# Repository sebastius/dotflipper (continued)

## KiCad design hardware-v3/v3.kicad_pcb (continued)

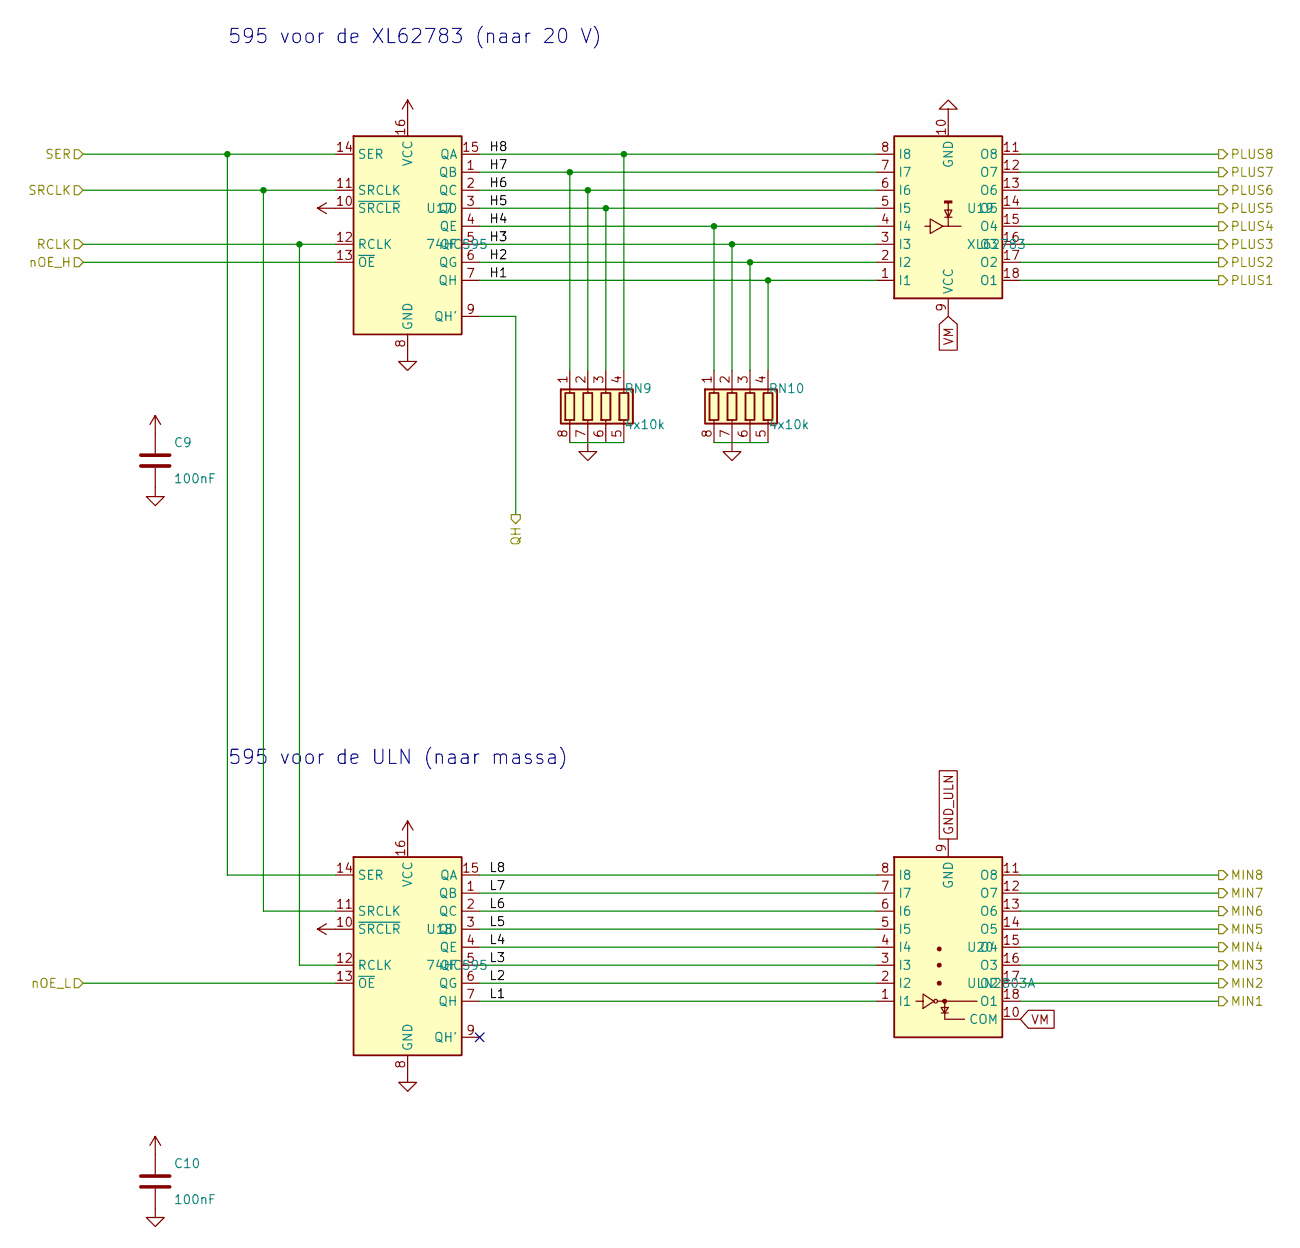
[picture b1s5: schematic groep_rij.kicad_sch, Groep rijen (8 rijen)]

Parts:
C9, C10: 100nF; C_0603_1608Metric; LCSC C14663
RN9, RN10: 4x10k; R_Array_Convex_4x0603; LCSC C29718
U17, U18: 74HC595; SOIC-16_3.9x9.9mm_P1.27mm; LCSC C5947
U19: XL62783; SOIC-18W_7.5x11.6mm_P1.27mm; LCSC C556260
U20: ULN2803A; SOIC-18W_7.5x11.6mm_P1.27mm; LCSC C845537

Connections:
+5V: C9.1, C10.1, U17.10 (~SRCLR), U17.16 (VCC), U18.10 (~SRCLR), U18.16 (VCC); also elsewhere on the board
/CHAIN4: U17.14 (SER), U18.14 (SER); also elsewhere on the board
/CHAIN5: U17.9 (QH'); also elsewhere on the board
/G5/H1: RN10.4 (R4.1), U17.7 (QH), U19.1 (I1)
/G5/H2: RN10.3 (R3.1), U17.6 (QG), U19.2 (I2)
/G5/H3: RN10.2 (R2.1), U17.5 (QF), U19.3 (I3)
/G5/H4: RN10.1 (R1.1), U17.4 (QE), U19.4 (I4)
/G5/H5: RN9.3 (R3.1), U17.3 (QD), U19.5 (I5)
/G5/H6: RN9.2 (R2.1), U17.2 (QC), U19.6 (I6)
/G5/H7: RN9.1 (R1.1), U17.1 (QB), U19.7 (I7)
/G5/H8: RN9.4 (R4.1), U17.15 (QA), U19.8 (I8)
/G5/L1: U18.7 (QH), U20.1 (I1)
/G5/L2: U18.6 (QG), U20.2 (I2)
/G5/L3: U18.5 (QF), U20.3 (I3)
/G5/L4: U18.4 (QE), U20.4 (I4)
/G5/L5: U18.3 (QD), U20.5 (I5)
/G5/L6: U18.2 (QC), U20.6 (I6)
/G5/L7: U18.1 (QB), U20.7 (I7)
/G5/L8: U18.15 (QA), U20.8 (I8)
/LATCH: U17.12 (RCLK), U18.12 (RCLK); also elsewhere on the board
/SCLK: U17.11 (SRCLK), U18.11 (SRCLK); also elsewhere on the board
/X3_1: U19.11 (O8); also elsewhere on the board
/X3_2: U20.11 (O8); also elsewhere on the board
/X3_3: U19.12 (O7); also elsewhere on the board
/X3_4: U20.12 (O7); also elsewhere on the board
/X3_5: U19.13 (O6); also elsewhere on the board
/X3_6: U20.13 (O6); also elsewhere on the board
/X3_7: U19.14 (O5); also elsewhere on the board
/X3_8: U20.14 (O5); also elsewhere on the board
/X3_9: U19.15 (O4); also elsewhere on the board
/X3_10: U20.15 (O4); also elsewhere on the board
/X3_11: U19.16 (O3); also elsewhere on the board
/X3_12: U20.16 (O3); also elsewhere on the board
/X3_13: U19.17 (O2); also elsewhere on the board
/X3_14: U20.17 (O2); also elsewhere on the board
/X3_15: U19.18 (O1); also elsewhere on the board
/X3_16: U20.18 (O1); also elsewhere on the board
/nOE_H_ROW: U17.13 (~OE); also elsewhere on the board
/nOE_L_ROW: U18.13 (~OE); also elsewhere on the board
GND: C9.2, C10.2, RN9.5 (R4.2), RN9.6 (R3.2), RN9.7 (R2.2), RN9.8 (R1.2), RN10.5 (R4.2), RN10.6 (R3.2), RN10.7 (R2.2), RN10.8 (R1.2), U17.8 (GND), U18.8 (GND), U19.10 (GND); also elsewhere on the board
GND_ULN: U20.9 (GND); also elsewhere on the board
VM: U19.9 (VCC), U20.10 (COM); also elsewhere on the board

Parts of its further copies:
C11, C12: 100nF; C_0603_1608Metric; LCSC C14663
RN11, RN12: 4x10k; R_Array_Convex_4x0603; LCSC C29718
U21, U22: 74HC595; SOIC-16_3.9x9.9mm_P1.27mm; LCSC C5947
U23: XL62783; SOIC-18W_7.5x11.6mm_P1.27mm; LCSC C556260
U24: ULN2803A; SOIC-18W_7.5x11.6mm_P1.27mm; LCSC C845537

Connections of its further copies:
+5V: C11.1, C12.1, U21.10 (~SRCLR), U21.16 (VCC), U22.10 (~SRCLR), U22.16 (VCC); also elsewhere on the board
/CHAIN5: U21.14 (SER), U22.14 (SER); also elsewhere on the board
/CHAIN_END: U21.9 (QH'); also elsewhere on the board
/G6/H1: RN12.4 (R4.1), U21.7 (QH), U23.1 (I1)
/G6/H2: RN12.3 (R3.1), U21.6 (QG), U23.2 (I2)
/G6/H3: RN12.2 (R2.1), U21.5 (QF), U23.3 (I3)
/G6/H4: RN12.1 (R1.1), U21.4 (QE), U23.4 (I4)
/G6/H5: RN11.3 (R3.1), U21.3 (QD), U23.5 (I5)
/G6/H6: RN11.2 (R2.1), U21.2 (QC), U23.6 (I6)
/G6/H7: RN11.1 (R1.1), U21.1 (QB), U23.7 (I7)
/G6/H8: RN11.4 (R4.1), U21.15 (QA), U23.8 (I8)
/G6/L1: U22.7 (QH), U24.1 (I1)
/G6/L2: U22.6 (QG), U24.2 (I2)
/G6/L3: U22.5 (QF), U24.3 (I3)
/G6/L4: U22.4 (QE), U24.4 (I4)
/G6/L5: U22.3 (QD), U24.5 (I5)
/G6/L6: U22.2 (QC), U24.6 (I6)
/G6/L7: U22.1 (QB), U24.7 (I7)
/G6/L8: U22.15 (QA), U24.8 (I8)
/LATCH: U21.12 (RCLK), U22.12 (RCLK); also elsewhere on the board
/SCLK: U21.11 (SRCLK), U22.11 (SRCLK); also elsewhere on the board
/X2_1: U23.11 (O8); also elsewhere on the board
/X2_2: U24.11 (O8); also elsewhere on the board
/X2_3: U23.12 (O7); also elsewhere on the board
/X2_4: U24.12 (O7); also elsewhere on the board
/X2_5: U23.13 (O6); also elsewhere on the board
/X2_6: U24.13 (O6); also elsewhere on the board
/X2_7: U23.14 (O5); also elsewhere on the board
/X2_8: U24.14 (O5); also elsewhere on the board
/X2_9: U23.15 (O4); also elsewhere on the board
/X2_10: U24.15 (O4); also elsewhere on the board
/X2_11: U23.16 (O3); also elsewhere on the board
/X2_12: U24.16 (O3); also elsewhere on the board
/X2_13: U23.17 (O2); also elsewhere on the board
/X2_14: U24.17 (O2); also elsewhere on the board
/X2_15: U23.18 (O1); also elsewhere on the board
/X2_16: U24.18 (O1); also elsewhere on the board
/nOE_H_ROW: U21.13 (~OE); also elsewhere on the board
/nOE_L_ROW: U22.13 (~OE); also elsewhere on the board
GND: C11.2, C12.2, RN11.5 (R4.2), RN11.6 (R3.2), RN11.7 (R2.2), RN11.8 (R1.2), RN12.5 (R4.2), RN12.6 (R3.2), RN12.7 (R2.2), RN12.8 (R1.2), U21.8 (GND), U22.8 (GND), U23.10 (GND); also elsewhere on the board
GND_ULN: U24.9 (GND); also elsewhere on the board
VM: U23.9 (VCC), U24.10 (COM); also elsewhere on the board

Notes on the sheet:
595 voor de XL62783 (naar 20 V)
595 voor de ULN (naar massa)

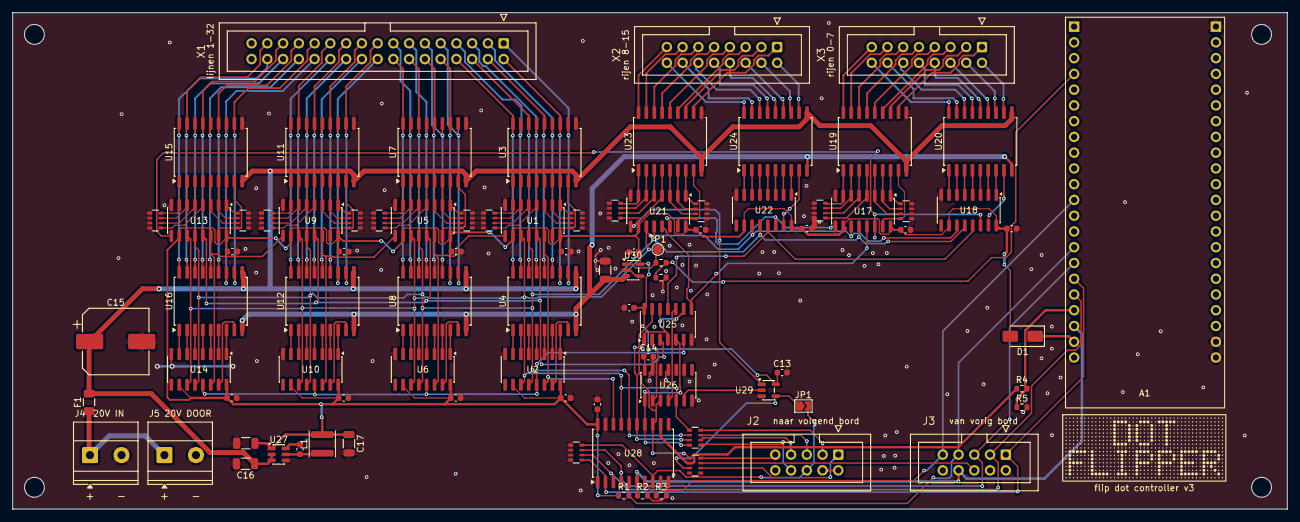
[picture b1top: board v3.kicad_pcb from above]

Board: 2 copper layers, 205.4 x 80.0 mm, 93 parts (0 on the bottom side), 206 nets.

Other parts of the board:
H1, H2, H3, H4: MountingHole_3.2mm_M3
LOGO1: Logo_Dotflipper

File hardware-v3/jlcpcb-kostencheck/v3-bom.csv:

Comment,Designator,Footprint,LCSC Part #
100nF,"C1,C10,C11,C12,C13,C14,C18,C19,C2,C20,C3,C4,C5,C6,C7,C8,C9",C_0603_1608Metric,C14663
470uF 35V,C15,CP_Elec_10x10.5,C46550413
10uF 50V,C16,C_1206_3216Metric,C13585
22uF 25V,"C17,C21",C_1206_3216Metric,C12891
SS14,D1,D_SMA,C2480
3A,F1,Fuse_1206_3216Metric,C182445
4.7uH,L1,L_Sunlord_SWPA4030S,C57269
10k,"R1,R4",R_0603_1608Metric,C25804
100k,"R2,R3",R_0603_1608Metric,C25803
20k,R5,R_0603_1608Metric,C4184
4x10k,"RN1,RN10,RN11,RN12,RN15,RN2,RN3,RN4,RN5,RN6,RN7,RN8,RN9",R_Array_Convex_4x0603,C29718
4x1k,"RN13,RN14",R_Array_Convex_4x0603,C20197
ULN2803A,"U12,U16,U20,U24,U4,U8",SOIC-18W_7.5x11.6mm_P1.27mm,C845537
XL62783,"U11,U15,U19,U23,U3,U7",SOIC-18W_7.5x11.6mm_P1.27mm,C556260
74HC32,U25,SOIC-14_3.9x8.7mm_P1.27mm,C5632
74HC14,U26,SOIC-14_3.9x8.7mm_P1.27mm,C5605
AP63205WU,U27,TSOT-23-6,C2071056
74AHCT541,U28,SOIC-20W_7.5x12.8mm_P1.27mm,C2682058
74LVC1G79,U29,SOT-23-5,C42878
74HC595,"U1,U10,U13,U14,U17,U18,U2,U21,U22,U5,U6,U9",SOIC-16_3.9x9.9mm_P1.27mm,C5947

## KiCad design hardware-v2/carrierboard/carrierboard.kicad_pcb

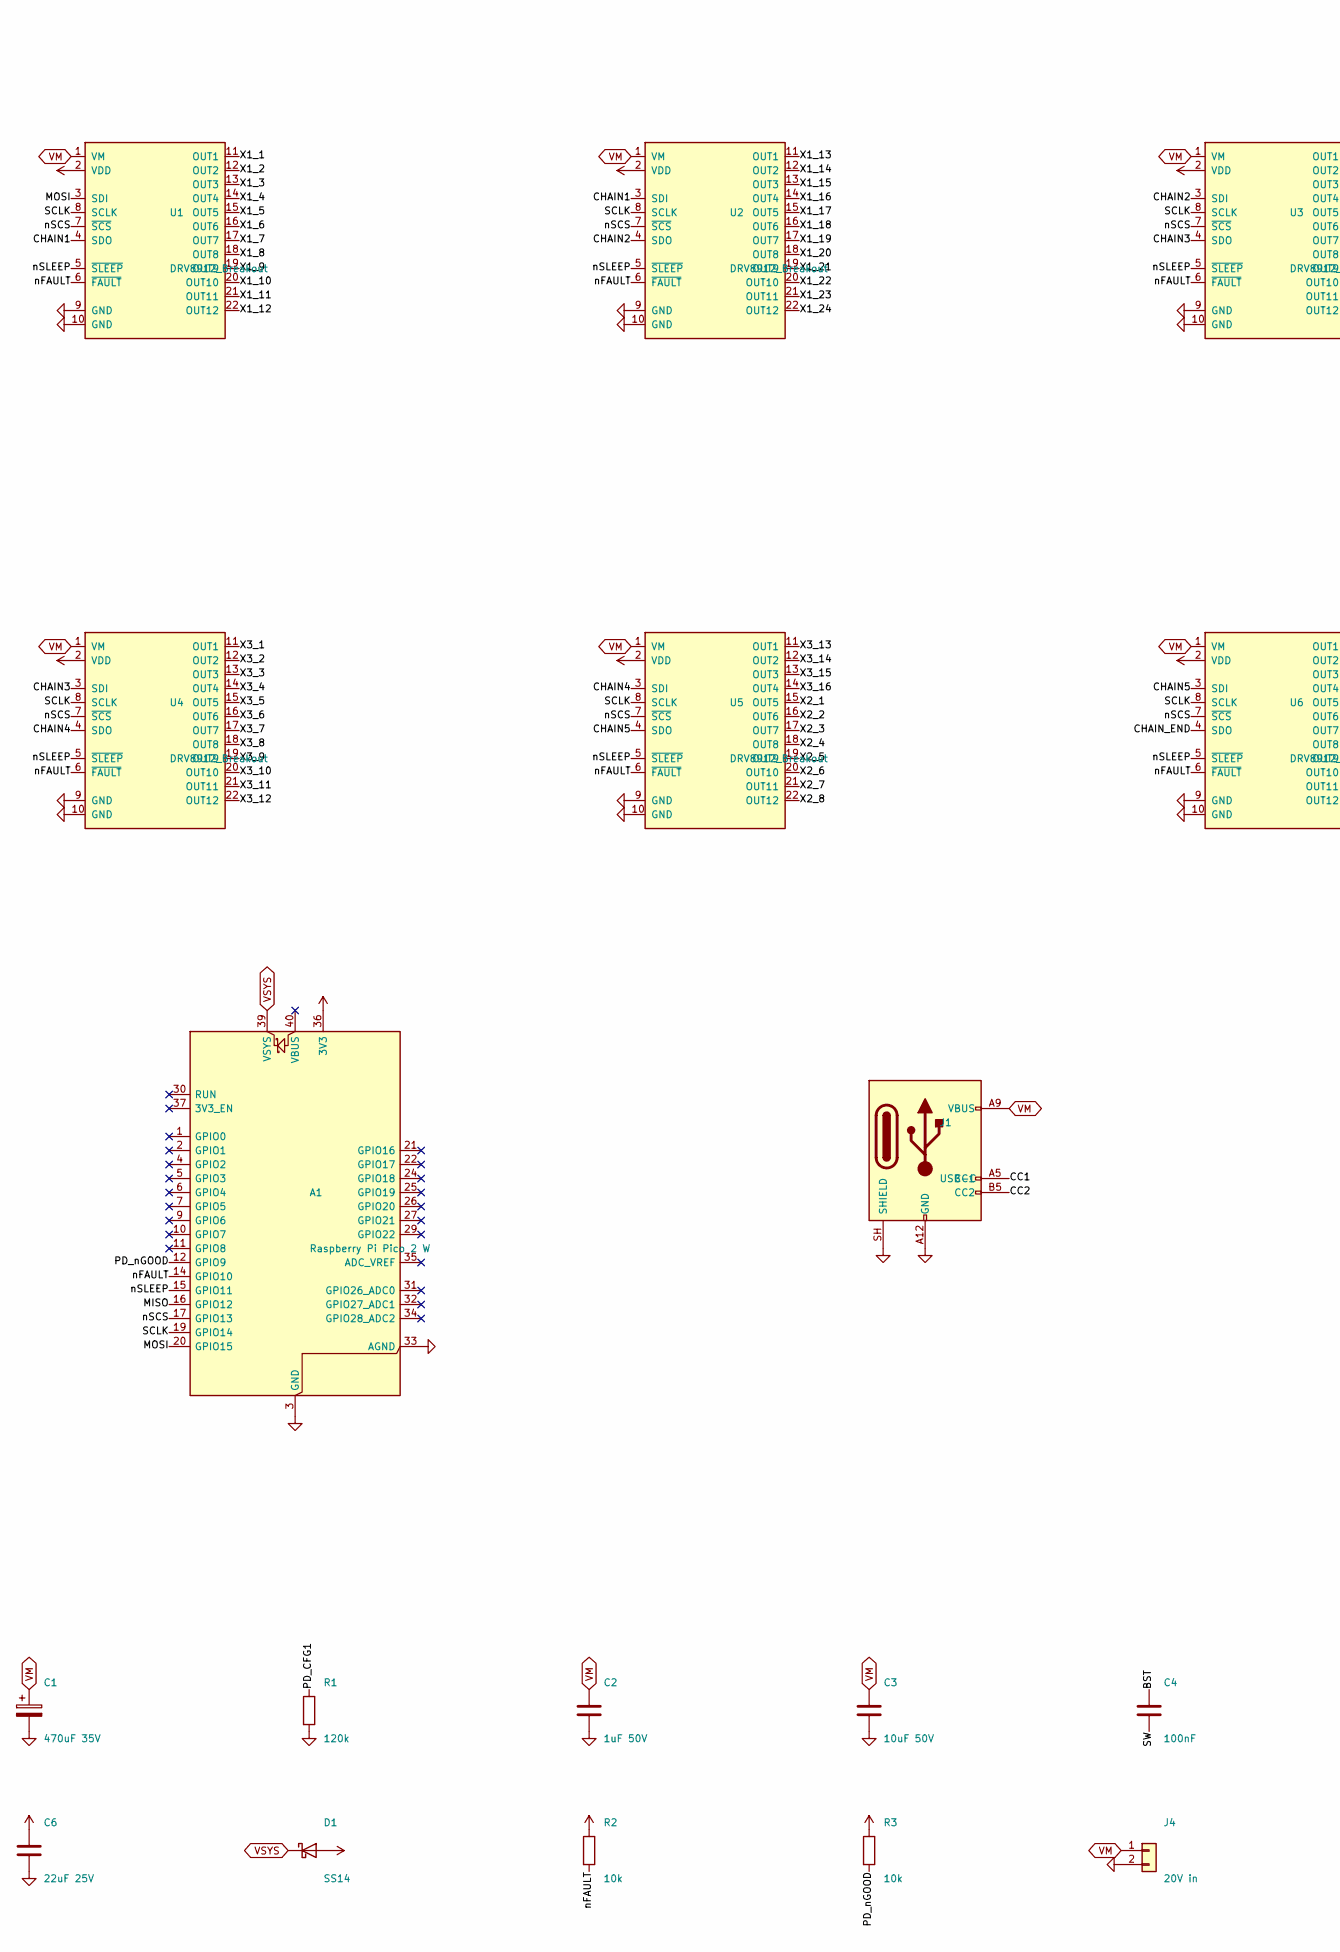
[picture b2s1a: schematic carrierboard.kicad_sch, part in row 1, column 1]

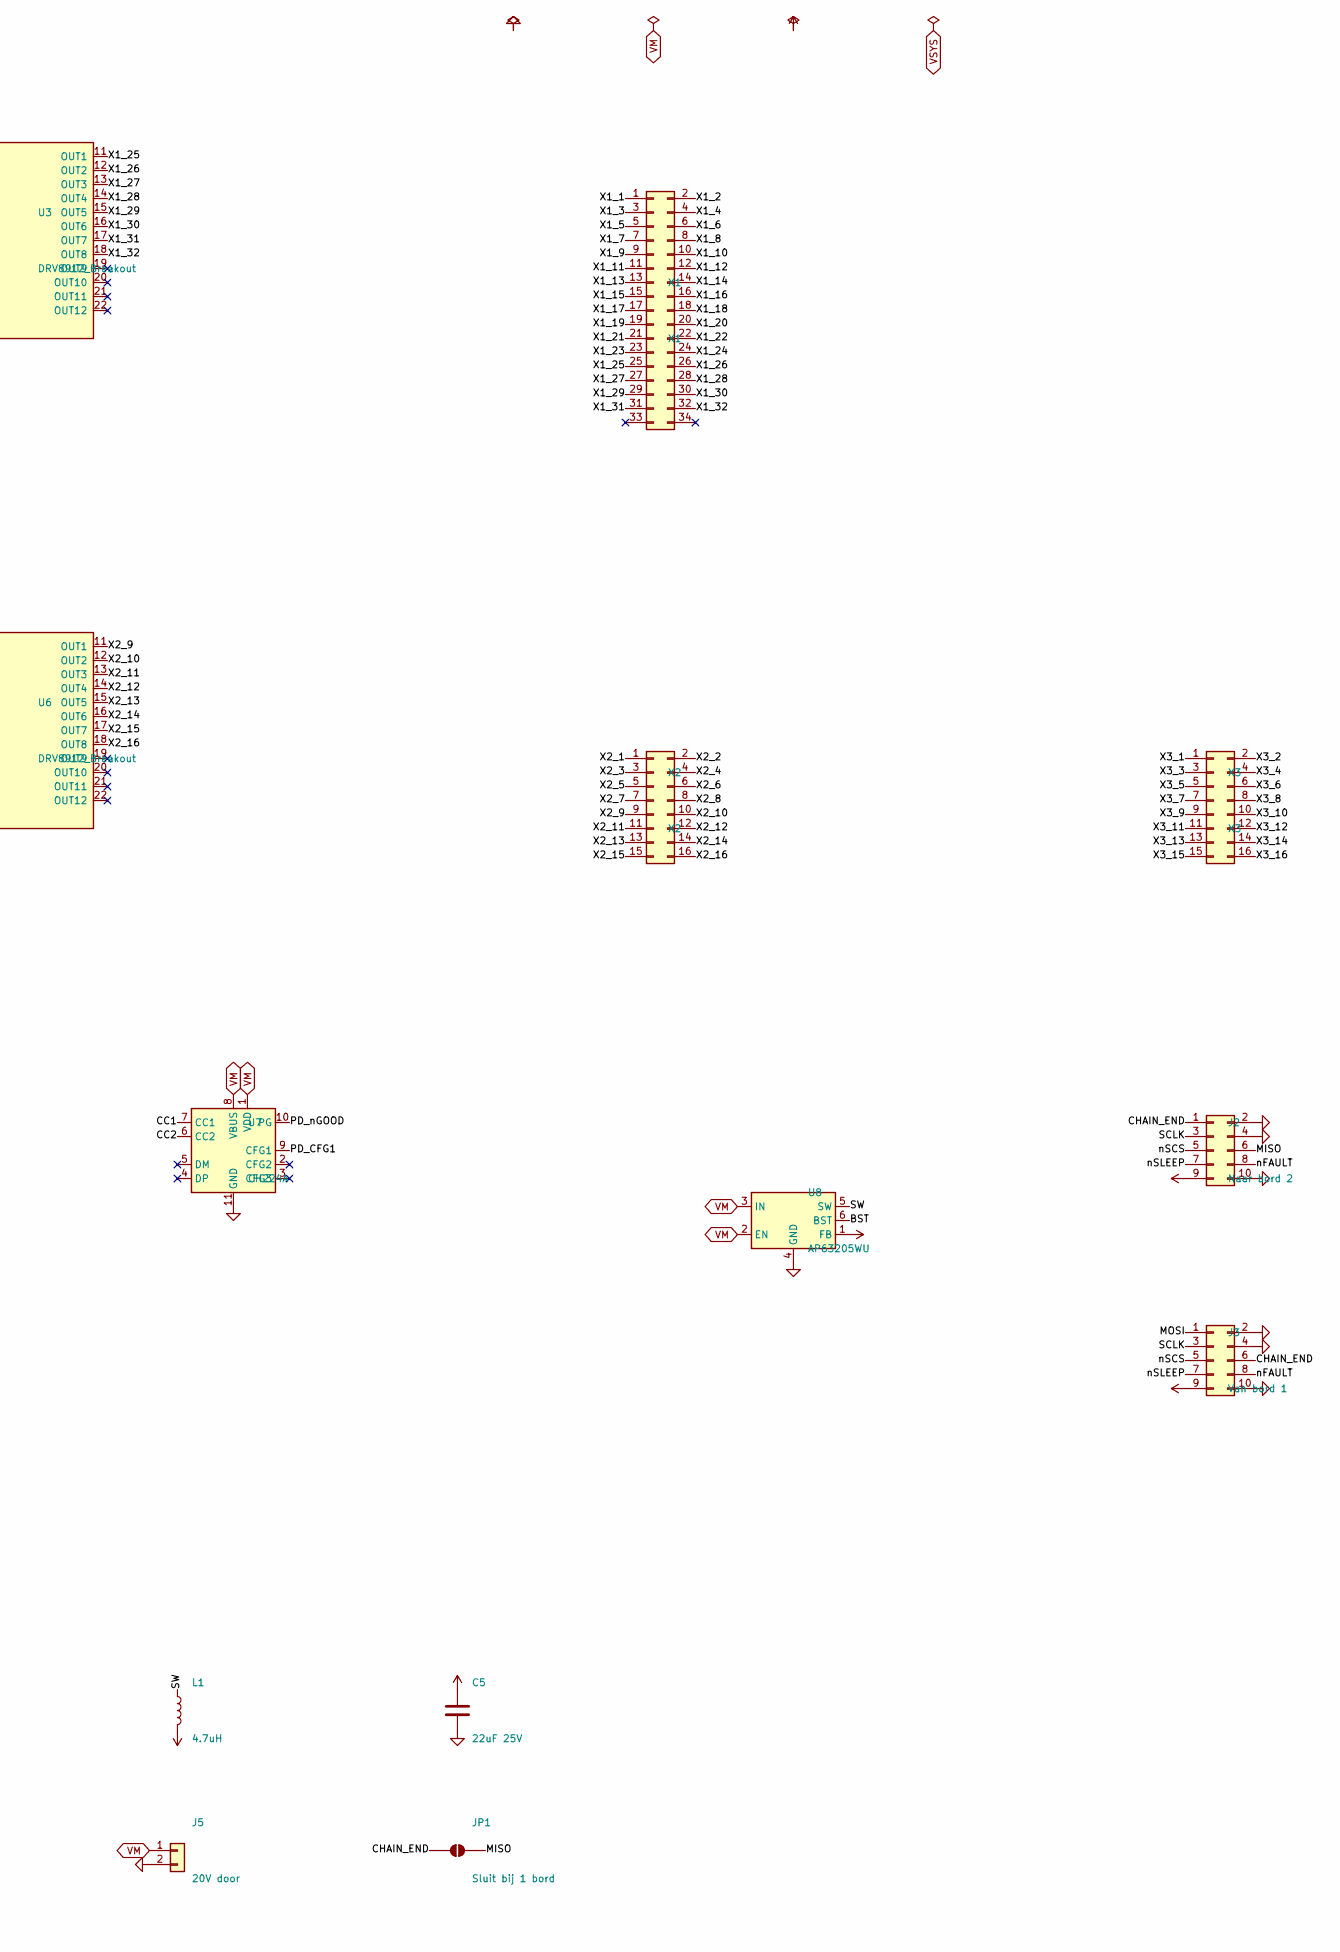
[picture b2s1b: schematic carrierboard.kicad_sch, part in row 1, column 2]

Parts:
A1: Raspberry Pi Pico 2 W; RaspberryPi_Pico_W_THT
C1: 470uF 35V; CP_Elec_10x10.5; LCSC C46550413
C2: 1uF 50V; C_0603_1608Metric; LCSC C15849
C3: 10uF 50V; C_1206_3216Metric; LCSC C89632
C4: 100nF; C_0603_1608Metric; LCSC C14663
C5, C6: 22uF 25V; C_1206_3216Metric; LCSC C12891
D1: SS14; D_SMA; LCSC C2480
J1: USB-C; USB_C_Receptacle_GCT_USB4125-xx-x-0190_6P_TopMnt_Horizontal; LCSC C5246813
J2: Naar bord 2; IDC-Header_2x05_P2.54mm_Vertical
J3: Van bord 1; IDC-Header_2x05_P2.54mm_Vertical
J4: 20V in; TerminalBlock_Phoenix_MKDS-1,5-2-5.08_1x02_P5.08mm_Horizont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
J5: 20V door; TerminalBlock_Phoenix_MKDS-1,5-2-5.08_1x02_P5.08mm_Horizont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
JP1: Sluit bij 1 bord; SolderJumper-2_P1.3mm_Open_TrianglePad1.0x1.5mm
L1: 4.7uH; L_Sunlord_SWPA5040S; LCSC C305174
R1: 120k; R_0603_1608Metric; LCSC C25808
R2, R3: 10k; R_0603_1608Metric; LCSC C25804
U1, U2, U3, U4, U5, U6: DRV8912_Breakout; DRV8912_Breakout_ChipDown
U7: CH224A; SSOP-10-1EP_3.9x4.9mm_P1mm_EP2.1x3.3mm; LCSC C42459160
U8: AP63205WU; TSOT-23-6; LCSC C2071056
X1: X1; IDC-Header_2x17_P2.54mm_Vertical
X2: X2; IDC-Header_2x08_P2.54mm_Vertical
X3: X3; IDC-Header_2x08_P2.54mm_Vertical

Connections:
+3V3: A1.36 (3V3), J2.9, J3.9, R2.1, R3.1, U1.2 (VDD), U2.2 (VDD), U3.2 (VDD), U4.2 (VDD), U5.2 (VDD), U6.2 (VDD)
+5V: C5.1, C6.1, D1.2 (A), L1.2, U8.1 (FB)
/BST: C4.1, U8.6 (BST)
/CC1: J1.A5 (CC1), U7.7 (CC1)
/CC2: J1.B5 (CC2), U7.6 (CC2)
/CHAIN1: U1.4 (SDO), U2.3 (SDI)
/CHAIN2: U2.4 (SDO), U3.3 (SDI)
/CHAIN3: U3.4 (SDO), U4.3 (SDI)
/CHAIN4: U4.4 (SDO), U5.3 (SDI)
/CHAIN5: U5.4 (SDO), U6.3 (SDI)
/CHAIN_END: J2.1, J3.6, JP1.1 (A), U6.4 (SDO)
/MISO: A1.16 (GPIO12), J2.6, JP1.2 (B)
/MOSI: A1.20 (GPIO15), J3.1, U1.3 (SDI)
/PD_CFG1: R1.1, U7.9 (CFG1)
/PD_nGOOD: A1.12 (GPIO9), R3.2, U7.10 (PG)
/SCLK: A1.19 (GPIO14), J2.3, J3.3, U1.8 (SCLK), U2.8 (SCLK), U3.8 (SCLK), U4.8 (SCLK), U5.8 (SCLK), U6.8 (SCLK)
/SW: C4.2, L1.1, U8.5 (SW)
/X1_1: U1.11 (OUT1), X1.1
/X1_2: U1.12 (OUT2), X1.2
/X1_3: U1.13 (OUT3), X1.3
/X1_4: U1.14 (OUT4), X1.4
/X1_5: U1.15 (OUT5), X1.5
/X1_6: U1.16 (OUT6), X1.6
/X1_7: U1.17 (OUT7), X1.7
/X1_8: U1.18 (OUT8), X1.8
/X1_9: U1.19 (OUT9), X1.9
/X1_10: U1.20 (OUT10), X1.10
/X1_11: U1.21 (OUT11), X1.11
/X1_12: U1.22 (OUT12), X1.12
/X1_13: U2.11 (OUT1), X1.13
/X1_14: U2.12 (OUT2), X1.14
/X1_15: U2.13 (OUT3), X1.15
/X1_16: U2.14 (OUT4), X1.16
/X1_17: U2.15 (OUT5), X1.17
/X1_18: U2.16 (OUT6), X1.18
/X1_19: U2.17 (OUT7), X1.19
/X1_20: U2.18 (OUT8), X1.20
/X1_21: U2.19 (OUT9), X1.21
/X1_22: U2.20 (OUT10), X1.22
/X1_23: U2.21 (OUT11), X1.23
/X1_24: U2.22 (OUT12), X1.24
/X1_25: U3.11 (OUT1), X1.25
/X1_26: U3.12 (OUT2), X1.26
/X1_27: U3.13 (OUT3), X1.27
/X1_28: U3.14 (OUT4), X1.28
/X1_29: U3.15 (OUT5), X1.29
/X1_30: U3.16 (OUT6), X1.30
/X1_31: U3.17 (OUT7), X1.31
/X1_32: U3.18 (OUT8), X1.32
/X2_1: U5.15 (OUT5), X2.1
/X2_2: U5.16 (OUT6), X2.2
/X2_3: U5.17 (OUT7), X2.3
/X2_4: U5.18 (OUT8), X2.4
/X2_5: U5.19 (OUT9), X2.5
/X2_6: U5.20 (OUT10), X2.6
/X2_7: U5.21 (OUT11), X2.7
/X2_8: U5.22 (OUT12), X2.8
/X2_9: U6.11 (OUT1), X2.9
/X2_10: U6.12 (OUT2), X2.10
/X2_11: U6.13 (OUT3), X2.11
/X2_12: U6.14 (OUT4), X2.12
/X2_13: U6.15 (OUT5), X2.13
/X2_14: U6.16 (OUT6), X2.14
/X2_15: U6.17 (OUT7), X2.15
/X2_16: U6.18 (OUT8), X2.16
/X3_1: U4.11 (OUT1), X3.1
/X3_2: U4.12 (OUT2), X3.2
/X3_3: U4.13 (OUT3), X3.3
/X3_4: U4.14 (OUT4), X3.4
/X3_5: U4.15 (OUT5), X3.5
/X3_6: U4.16 (OUT6), X3.6
/X3_7: U4.17 (OUT7), X3.7
/X3_8: U4.18 (OUT8), X3.8
/X3_9: U4.19 (OUT9), X3.9
/X3_10: U4.20 (OUT10), X3.10
/X3_11: U4.21 (OUT11), X3.11
/X3_12: U4.22 (OUT12), X3.12
/X3_13: U5.11 (OUT1), X3.13
/X3_14: U5.12 (OUT2), X3.14
/X3_15: U5.13 (OUT3), X3.15
/X3_16: U5.14 (OUT4), X3.16
/nFAULT: A1.14 (GPIO10), J2.8, J3.8, R2.2, U1.6 (~FAULT), U2.6 (~FAULT), U3.6 (~FAULT), U4.6 (~FAULT), U5.6 (~FAULT), U6.6 (~FAULT)
/nSCS: A1.17 (GPIO13), J2.5, J3.5, U1.7 (~SCS), U2.7 (~SCS), U3.7 (~SCS), U4.7 (~SCS), U5.7 (~SCS), U6.7 (~SCS)
/nSLEEP: A1.15 (GPIO11), J2.7, J3.7, U1.5 (~SLEEP), U2.5 (~SLEEP), U3.5 (~SLEEP), U4.5 (~SLEEP), U5.5 (~SLEEP), U6.5 (~SLEEP)
GND: A1.3 (GND), A1.8 (GND), A1.13 (GND), A1.18 (GND), A1.23 (GND), A1.28 (GND), A1.33 (AGND), A1.38 (GND), C1.2, C2.2, C3.2, C5.2, C6.2, J1.A12 (GND), J1.B12 (GND), J1.SH (SHIELD), J2.2, J2.4, J2.10, J3.2, J3.4, J3.10, J4.2, J5.2, R1.2, U1.9 (GND), U1.10 (GND), U2.9 (GND), U2.10 (GND), U3.9 (GND), U3.10 (GND), U4.9 (GND), U4.10 (GND), U5.9 (GND), U5.10 (GND), U6.9 (GND), U6.10 (GND), U7.11 (GND), U8.4 (GND)
VM: C1.1, C2.1, C3.1, J1.A9 (VBUS), J1.B9 (VBUS), J4.1, J5.1, U1.1 (VM), U2.1 (VM), U3.1 (VM), U4.1 (VM), U5.1 (VM), U6.1 (VM), U7.1 (VDD), U7.8 (VBUS), U8.2 (EN), U8.3 (IN)
VSYS: A1.39 (VSYS), D1.1 (K)

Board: 2 copper layers, 33 parts (0 on the bottom side), 87 nets, no tracks yet.

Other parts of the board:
H1, H2, H3, H4: MountingHole_3.2mm_M3

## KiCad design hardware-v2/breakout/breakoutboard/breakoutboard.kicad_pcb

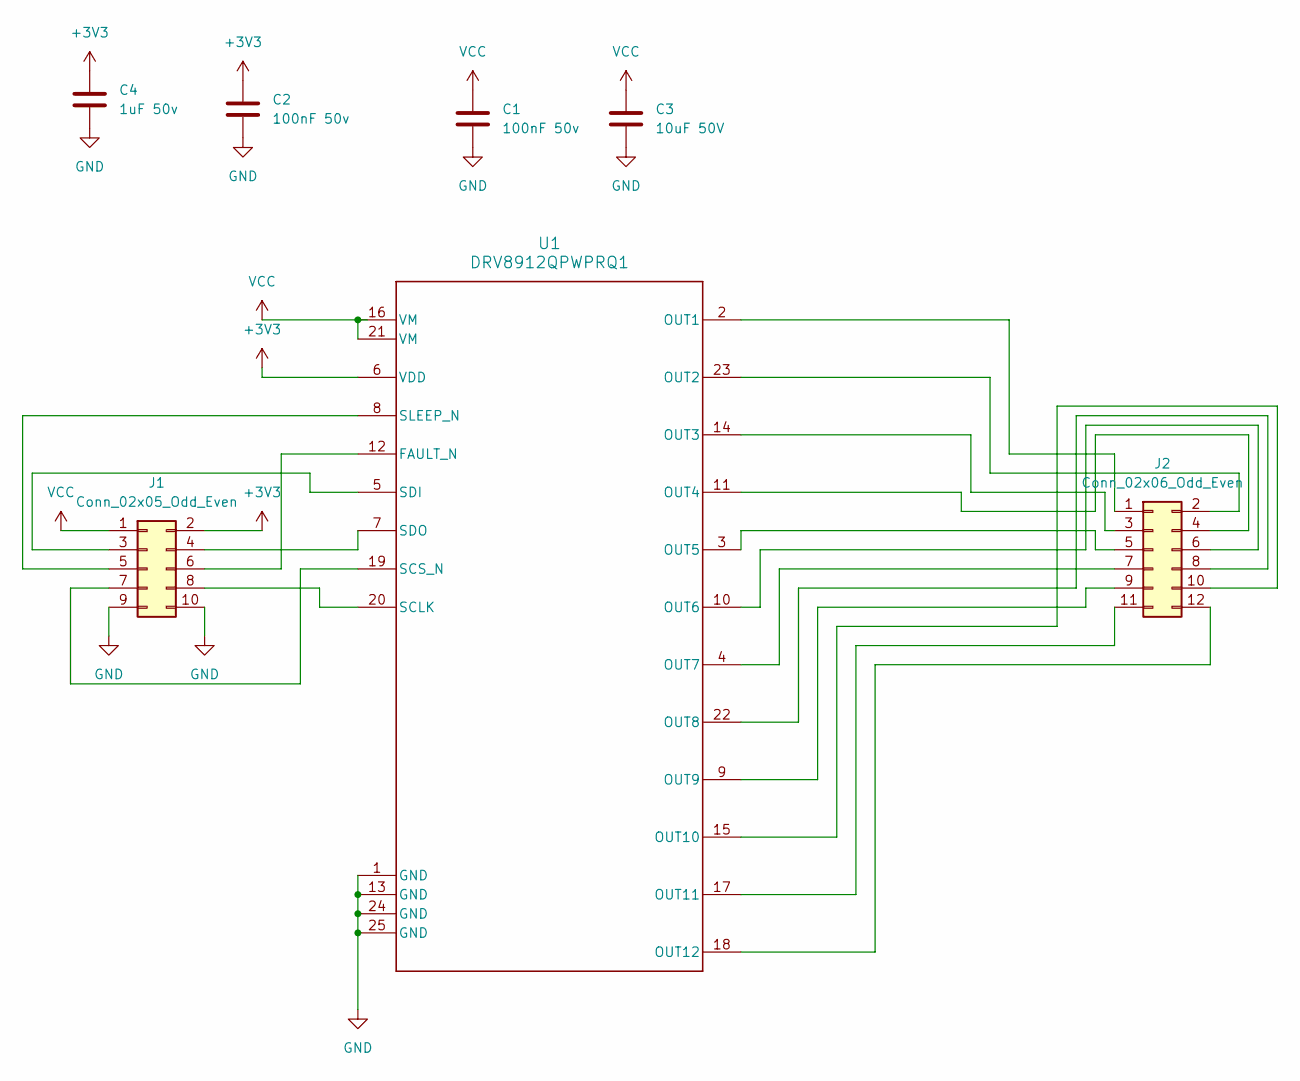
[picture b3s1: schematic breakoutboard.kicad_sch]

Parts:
C1, C2: 100nF 50v; C_0603_1608Metric; LCSC C14663
C3: 10uF 50V; C_1206_3216Metric; LCSC C89632
C4: 1uF 50v; C_0603_1608Metric; LCSC C15849
J1: Conn_02x05_Odd_Even; PinHeader_2x05_P2.54mm_Vertical
J2: Conn_02x06_Odd_Even; PinHeader_2x06_P2.54mm_Vertical
U1: DRV8912QPWPRQ1; PWP0024N_L; LCSC C1855817

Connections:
+3V3: C2.1, C4.1, J1.2, U1.6 (VDD)
GND: C1.2, C2.2, C3.2, C4.2, J1.9, J1.10, U1.1 (GND), U1.13 (GND), U1.24 (GND), U1.25 (GND)
unnamed: J1.3, U1.5 (SDI)
unnamed: J1.4, U1.7 (SDO)
unnamed: J1.5, U1.8 (SLEEP_N)
unnamed: J1.6, U1.12 (FAULT_N)
unnamed: J1.7, U1.19 (SCS_N)
unnamed: J1.8, U1.20 (SCLK)
unnamed: J2.1, U1.2 (OUT1)
unnamed: J2.2, U1.23 (OUT2)
unnamed: J2.3, U1.14 (OUT3)
unnamed: J2.4, U1.11 (OUT4)
unnamed: J2.5, U1.3 (OUT5)
unnamed: J2.6, U1.10 (OUT6)
unnamed: J2.7, U1.4 (OUT7)
unnamed: J2.8, U1.22 (OUT8)
unnamed: J2.9, U1.9 (OUT9)
unnamed: J2.10, U1.15 (OUT10)
unnamed: J2.11, U1.17 (OUT11)
unnamed: J2.12, U1.18 (OUT12)
VCC: C1.1, C3.1, J1.1, U1.16 (VM), U1.21 (VM)

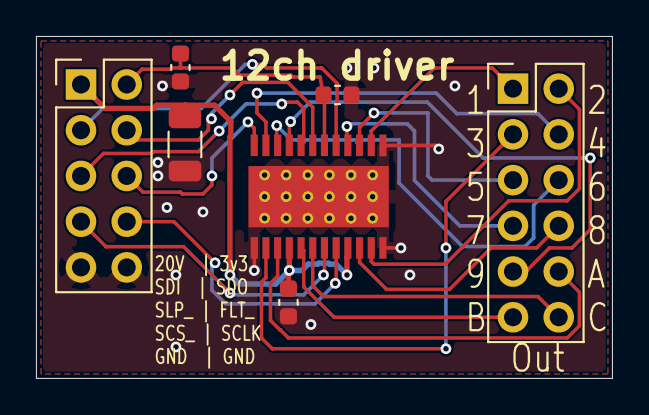
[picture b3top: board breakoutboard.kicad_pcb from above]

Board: 2 copper layers, 32.0 x 19.0 mm, 7 parts (0 on the bottom side), 21 nets.

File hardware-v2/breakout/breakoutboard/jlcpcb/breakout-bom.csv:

Comment,Designator,Footprint,LCSC Part #
100nF 50v,"C1,C2",C_0603_1608Metric,C14663
10uF 50V,C3,C_1206_3216Metric,C89632
1uF 50v,C4,C_0603_1608Metric,C15849
DRV8912QPWPRQ1,U1,PWP0024N_L,C1855817

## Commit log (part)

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2018-07-30 Readability and more explanation of how to flip a bit based on boolean color
2018-07-30 Minor cleanup of schematic. Made PDFs for those without Eagle.
2018-08-08 Extra beveligingen ingebouwd Code netter gemaakt (vind ik) Ik kan nog steeds niet mooie commitmessages maken
2018-08-08 adress -> address
2018-08-08 added units to defines, did a little less ternary for improved readability, thanks Joepie91 and Smeding
2018-08-08 More nitpicking to improve readabilty and prevent stupid errors
2018-08-08 ik mag van Eightdot geen strings concatenaten :'(
2018-08-08 Game of Life added
2018-08-08 added a few experiments in screen wipes to the main loop
2018-08-11 Beetje zitten rommelen met effectjes bedenken
2018-08-11 updated safety in void flipdot()
2018-09-01 SNAKES NOT ON A PLANE
2018-09-01 stomme time rename naar mytime
2018-09-02 twee variabelen die niet gebruikt werden weg. Verplaatsen uitlezen joystick naar eigen void. Nog niet af.
2019-05-17 nu incl UDP
2019-05-17 Show the IP address on the matrix when connected
2019-05-17 tetris begint
2019-05-18 tetris werkend
2019-06-16 datasheet toegevoegd
2019-06-16 Simultaan twee dots updaten van 2 panelen.
2019-08-27 updated README.md for more fun
2020-03-29 Update esp_flipdot.ino
    Incredible speed improvement
2020-03-29 Update esp_flipdot.ino
    Some cleanup
2020-03-30 Update esp_flipdot.ino
    OTA works after an incredible ordeal. Also updated GoL a bit to have regular intervals (75ms), looks better that way.
